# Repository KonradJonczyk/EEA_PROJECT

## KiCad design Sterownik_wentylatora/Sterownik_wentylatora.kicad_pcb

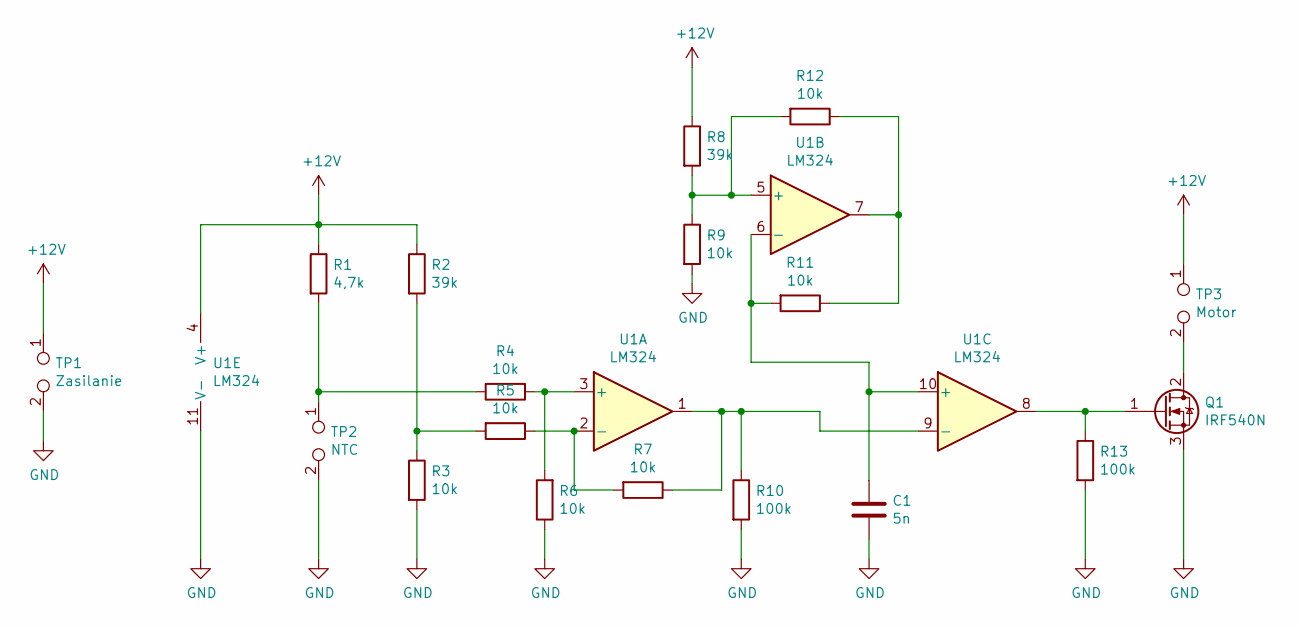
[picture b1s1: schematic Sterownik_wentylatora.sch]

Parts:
C1: 5n; C_Disc_D5.0mm_W2.5mm_P5.00mm
Q1: IRF540N; TO-220-3_Vertical
R1: 4,7k; R_Axial_DIN0204_L3.6mm_D1.6mm_P7.62mm_Horizontal
R2, R8: 39k; R_Axial_DIN0204_L3.6mm_D1.6mm_P7.62mm_Horizontal
R3, R4, R5, R6, R7, R9, R11, R12: 10k; R_Axial_DIN0204_L3.6mm_D1.6mm_P7.62mm_Horizontal
R10, R13: 100k; R_Axial_DIN0204_L3.6mm_D1.6mm_P7.62mm_Horizontal
TP1: Zasilanie; SolderWire-1.5sqmm_1x02_P7.8mm_D1.7mm_OD3.9mm
TP2: NTC; SolderWire-0.15sqmm_1x02_P4mm_D0.5mm_OD1.5mm
TP3: Motor; SolderWire-0.75sqmm_1x02_P7mm_D1.25mm_OD3.5mm
U1: LM324; DIP-14_W7.62mm

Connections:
+12V: R1.1, R2.1, R8.1, TP1.1, TP3.1, U1.4 (V+)
GND: C1.2, Q1.3 (S), R3.2, R6.1, R9.2, R10.2, R13.2, TP1.2, TP2.2, U1.11 (V-)
unnamed: C1.1, R11.2, U1.6 (-), U1.10 (+)
unnamed: Q1.1 (G), R13.1, U1.8
unnamed: Q1.2 (D), TP3.2
unnamed: R1.2, R4.2, TP2.1
unnamed: R2.2, R3.1, R5.2
unnamed: R4.1, R6.2, U1.3 (+)
unnamed: R5.1, R7.2, U1.2 (-)
unnamed: R7.1, R10.1, U1.1, U1.9 (-)
unnamed: R11.1, R12.1, U1.7
unnamed: R8.2, R9.1, R12.2, U1.5 (+)

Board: 2 copper layers, 19 parts (0 on the bottom side), 12 nets, no tracks yet.

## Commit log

2021-10-22 v_08
